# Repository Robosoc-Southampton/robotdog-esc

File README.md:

# Robot dog ESC

This is the repo for a FOC-based motor driver for a drone motor.

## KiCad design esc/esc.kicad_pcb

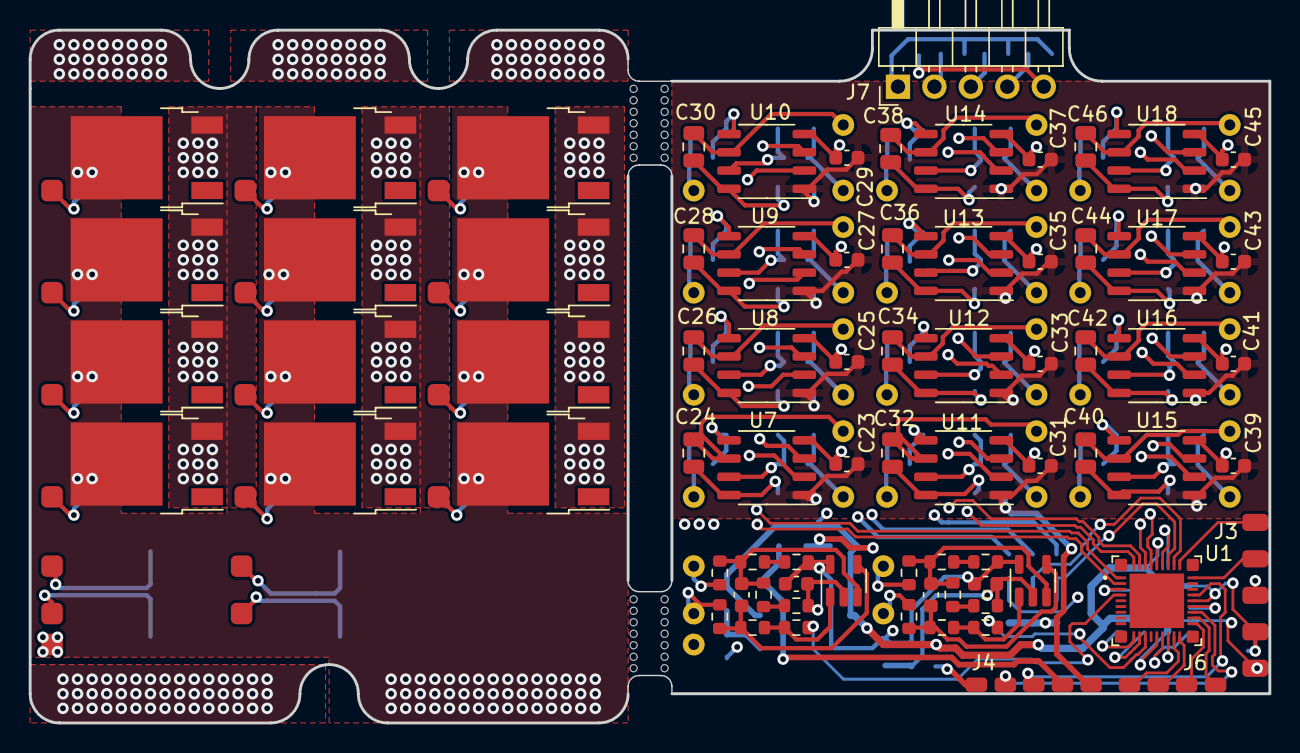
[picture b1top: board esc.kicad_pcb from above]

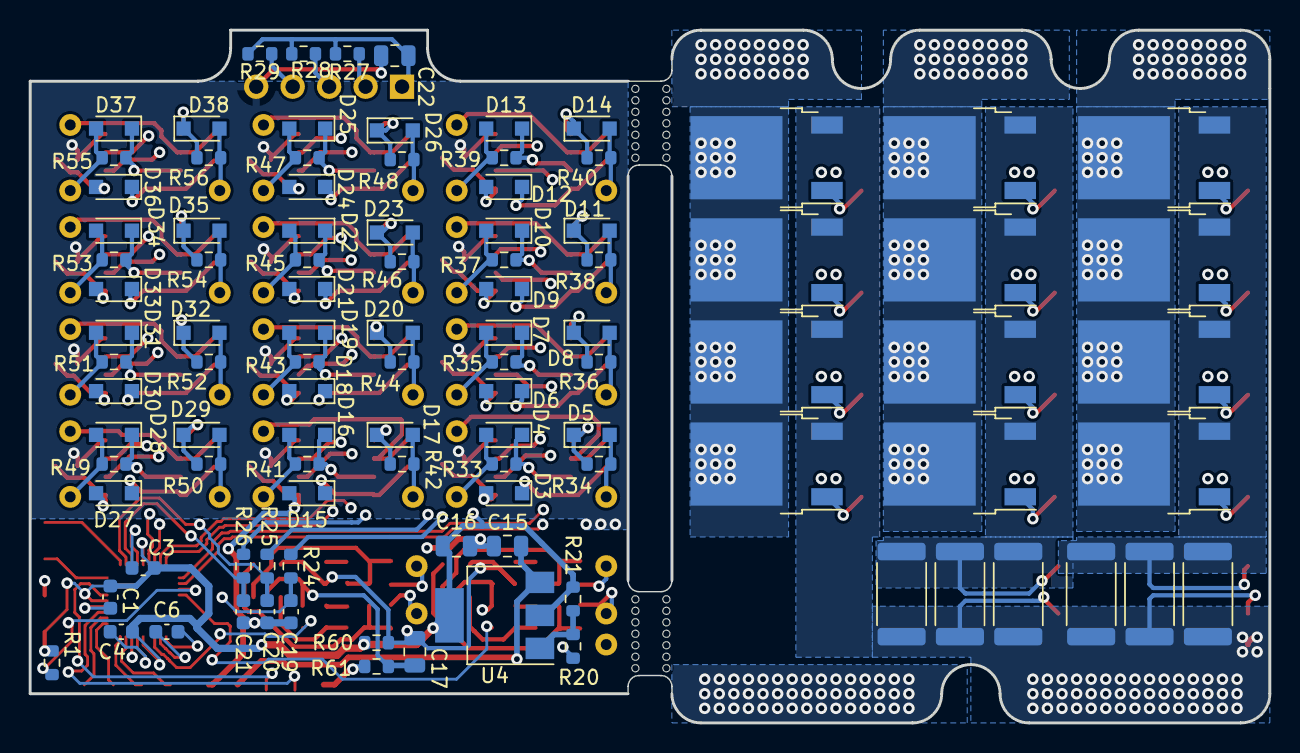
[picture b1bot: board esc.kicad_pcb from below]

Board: 4 copper layers, 86.4 x 48.3 mm, 234 parts (101 on the bottom side), 135 nets.

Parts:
C1, C3, C4, C6, C12, C13, C23, C25, C27, C29, C31, C33, C35, C37, C39, C41, C43, C45: 100n; C_0603_1608Metric
C8, C9, C19, C20, C21: 1n; C_0603_1608Metric
C15, C16, C17, C22, C24, C26, C28, C30, C32, C34, C36, C38, C40, C42, C44, C46: 10u; C_0805_2012Metric
D3, D4, D5, D6, D7, D8, D9, D10, D11, D12, D13, D14, D15, D16, D17, D18, D19, D20, D21, D22, D23, D24, D25, D26, D27, D28, D29, D30, D31, D32, D33, D34, D35, D36, D37, D38: 1N5819WS; D_SOD-323_HandSoldering
J3: Conn_01x05; ProgConnector
J4: Conn_01x05; EdgeConnector_5
J6: Conn_01x04; EdgeConnector_4
J7: Conn_01x05; PinHeader_1x05_P2.54mm_Horizontal
J8, J9, J10, J11, J17, J23, J29, J35, J41, J47, J53, J59, J65, J71, J77, J83, J88: Conn_01x01; SmallPad
J12, J13, J14, J18, J19, J20, J24, J25, J26, J30, J31, J32, J36, J37, J38, J42, J43, J44, J48, J49, J50, J54, J55, J56, J60, J61, J62, J66, J67, J68, J72, J73, J74, J78, J79, J80, J84, J85, J86, J87, J89: Conn_01x01; SmallPin
Q1, Q2, Q3, Q4, Q5, Q6, Q7, Q8, Q9, Q10, Q11, Q12, Q13, Q14, Q15, Q16, Q17, Q18, Q19, Q20, Q21, Q22, Q23, Q24: Q_NMOS_GDS; TO-252-2
R1: 10k; R_0603_1608Metric
R2, R3, R4, R5, R6, R7: 3m; R_2512_6332Metric
R8, R9, R10, R11: 120; R_0603_1608Metric
R16, R17, R18, R19, R22, R23, R30, R31, R32, R59: 3.3k; R_0603_1608Metric
R20: 1.5k; R_0603_1608Metric
R21, R24, R25, R26, R27, R28, R29: 1k; R_0603_1608Metric
R33, R34, R35, R36, R37, R38, R39, R40, R41, R42, R43, R44, R45, R46, R47, R48, R49, R50, R51, R52, R53, R54, R55, R56: 15; R_0603_1608Metric
R57, R58: 33; R_0603_1608Metric
R60, R61: 0R; R_0603_1608Metric
U1: dsPIC33CK64MC103; UQFN-36
U2, U3: GS8051; TSOT-23-5
U4: AP1117-ADJ; SOT-223-3_TabPin2
U7, U8, U9, U10, U11, U12, U13, U14, U15, U16, U17, U18: EG2131; SOP-8_3.9x4.9mm_P1.27mm

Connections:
+3.3VA: C6.1, C12.1, C13.1, C17.1, R30.2, R32.1, R60.2, U1.10 (AVDD), U2.5 (V+), U3.5 (V+)
+3V3: C1.2, C3.2, C4.2, C16.1, C22.1, J3.2, J7.1, R1.1, R21.1, R27.1, R28.1, R29.1, R60.1, U1.14 (VDD), U1.23 (VDD), U1.32 (VDD), U4.2 (VO)
+5V: C15.1, J4.4, U4.3 (VI)
+12V: C23.1, C25.1, C27.1, C29.1, C31.1, C33.1, C35.1, C37.1, C39.1, C41.1, C43.1, C45.1, D3.2 (A), D6.2 (A), D9.2 (A), D12.2 (A), D15.2 (A), D18.2 (A), D21.2 (A), D24.2 (A), D27.2 (A), D30.2 (A), D33.2 (A), D36.2 (A), J4.5, U7.1 (VCC), U8.1 (VCC), U9.1 (VCC), U10.1 (VCC), U11.1 (VCC), U12.1 (VCC), U13.1 (VCC), U14.1 (VCC), U15.1 (VCC), U16.1 (VCC), U17.1 (VCC), U18.1 (VCC)
/GPIO0: J6.1, U1.17 (OSCI/CLKI/AN5/RP32/RB0)
/GPIO1: J6.2, U1.18 (OSCO/CLKO/AN6/RP33/RB1)
/GPIO2: J6.3, U1.19 (OA2OUT/AN1/AN7/CMP1D/RP34/INT0/RB2)
/GPIO3: J6.4, U1.20 (PGD2/OA2IN-/AN8/RP35/RB3)
/HOME/HALL_C: C21.1, R26.1, U1.30 (RP53/RC5)
/I2C_SCL: J4.2, U1.21 (PGC2/OA2IN+/RP36/RB4)
/I2C_SDA: J4.3, U1.24 (PGD3/RP37/RB5)
/PGC1: J3.5, U1.28 (PGC1/AN11/RP41/SDA1/RB9)
/PGD1: J3.4, U1.27 (PGD1/AN10/RP40/SCL1/RB8)
/Phases/A_CURRENT_SENSE: R57.1, U1.4 (AN12/RP48/RC0)
/Phases/A_HIN: U1.1 (RP46/PWM1H/RB14), U7.2 (HIN), U8.2 (HIN), U9.2 (HIN), U10.2 (HIN)
/Phases/B_CURRENT_SENSE: R58.1, U1.12 (OA3IN-/AN13/CMP1B/ISRC0/RP49/RC1)
/Phases/B_HIN: U1.35 (TDI/RP44/PWM2H/RB12), U11.2 (HIN), U12.2 (HIN), U13.2 (HIN), U14.2 (HIN)
/Phases/C_HIN: U1.33 (TMS/RP42/PWM3H/RB10), U15.2 (HIN), U16.2 (HIN), U17.2 (HIN), U18.2 (HIN)
/Phases/PHASE_A: Q1.3 (S), Q2.2 (D), Q3.3 (S), Q4.2 (D), Q5.3 (S), Q6.2 (D), Q7.3 (S), Q8.2 (D)
/Phases/PHASE_B: Q9.3 (S), Q10.2 (D), Q11.3 (S), Q12.2 (D), Q13.3 (S), Q14.2 (D), Q15.3 (S), Q16.2 (D)
/Phases/PHASE_C: Q17.3 (S), Q18.2 (D), Q19.3 (S), Q20.2 (D), Q21.3 (S), Q22.2 (D), Q23.3 (S), Q24.2 (D)
/Phases/Phase A/BRIDGE_LOW: J8.1, Q2.3 (S), Q4.3 (S), Q6.3 (S), Q8.3 (S), R2.1, R3.1, R4.1
/Phases/Phase B/BRIDGE_LOW: J10.1, Q10.3 (S), Q12.3 (S), Q14.3 (S), Q16.3 (S), R5.1, R6.1, R7.1
/Phases/~A_LIN: U1.2 (RP47/PWM1L/RB15), U7.3 (~LIN), U8.3 (~LIN), U9.3 (~LIN), U10.3 (~LIN)
/Phases/~B_LIN: U1.36 (RP45/PWM2L/RB13), U11.3 (~LIN), U12.3 (~LIN), U13.3 (~LIN), U14.3 (~LIN)
/Phases/~C_LIN: U1.34 (TCK/RP43/PWM3L/RB11), U15.3 (~LIN), U16.3 (~LIN), U17.3 (~LIN), U18.3 (~LIN)
/QEI_A/HALL_A: C19.1, R24.1, U1.16 (AN15/IBIAS2/RP51/RC3)
/QEI_B/HALL_B: C20.1, R25.1, U1.29 (RP52/RC4)
/~MCLR: J3.1, R1.2, U1.3 (~MCLR)
GND: C1.1, C3.1, C4.1, C15.2, C16.2, C19.2, C20.2, C21.2, C22.2, C23.2, C25.2, C27.2, C29.2, C31.2, C33.2, C35.2, C37.2, C39.2, C41.2, C43.2, C45.2, J3.3, J4.1, J7.5, J89.1, R20.2, R61.1, U1.15 (VSS), U1.22 (VSS), U1.31 (VSS), U7.4 (COM), U8.4 (COM), U9.4 (COM), U10.4 (COM), U11.4 (COM), U12.4 (COM), U13.4 (COM), U14.4 (COM), U15.4 (COM), U16.4 (COM), U17.4 (COM), U18.4 (COM)
GNDA: C6.2, C12.2, C13.2, C17.2, R31.1, R59.2, R61.2, U1.11 (AVSS), U2.2 (V-), U3.2 (V-)
GNDPWR: J9.1, J11.1, J88.1, Q18.3 (S), Q20.3 (S), Q22.3 (S), Q24.3 (S), R2.2, R3.2, R4.2, R5.2, R6.2, R7.2
unnamed: C8.1, R8.1, R16.1, R17.2, U2.3 (+)
unnamed: C8.2, R9.1, R22.2, U2.4 (-)
unnamed: C9.1, R10.1, R18.1, R19.2, U3.3 (+)
unnamed: C9.2, R11.1, R23.2, U3.4 (-)
unnamed: C24.1, D3.1 (K), U7.8 (VB)
unnamed: C24.2, J13.1, U7.6 (VS)
unnamed: C26.1, D6.1 (K), U8.8 (VB)
unnamed: C26.2, J19.1, U8.6 (VS)
unnamed: C28.1, D9.1 (K), U9.8 (VB)
unnamed: C28.2, J25.1, U9.6 (VS)
unnamed: C30.1, D12.1 (K), U10.8 (VB)
unnamed: C30.2, J31.1, U10.6 (VS)
unnamed: C32.1, D15.1 (K), U11.8 (VB)
unnamed: C32.2, J37.1, U11.6 (VS)
unnamed: C34.1, D18.1 (K), U12.8 (VB)
unnamed: C34.2, J43.1, U12.6 (VS)
unnamed: C36.1, D21.1 (K), U13.8 (VB)
unnamed: C36.2, J49.1, U13.6 (VS)
unnamed: C38.1, D24.1 (K), U14.8 (VB)
unnamed: C38.2, J55.1, U14.6 (VS)
unnamed: C40.1, D27.1 (K), U15.8 (VB)
unnamed: C40.2, J61.1, U15.6 (VS)
unnamed: C42.1, D30.1 (K), U16.8 (VB)
unnamed: C42.2, J67.1, U16.6 (VS)
unnamed: C44.1, D33.1 (K), U17.8 (VB)
unnamed: C44.2, J73.1, U17.6 (VS)
unnamed: C46.1, D36.1 (K), U18.8 (VB)
unnamed: C46.2, J79.1, U18.6 (VS)
unnamed: D4.1 (K), R33.1, U7.7 (HO)
unnamed: D4.2 (A), J12.1, R33.2
unnamed: D5.1 (K), R34.1, U7.5 (LO)
unnamed: D5.2 (A), J14.1, R34.2
unnamed: D7.1 (K), R35.1, U8.7 (HO)
unnamed: D7.2 (A), J18.1, R35.2
unnamed: D8.1 (K), R36.1, U8.5 (LO)
unnamed: D8.2 (A), J20.1, R36.2
unnamed: D10.1 (K), R37.1, U9.7 (HO)
unnamed: D10.2 (A), J24.1, R37.2
unnamed: D11.1 (K), R38.1, U9.5 (LO)
unnamed: D11.2 (A), J26.1, R38.2
unnamed: D13.1 (K), R39.1, U10.7 (HO)
unnamed: D13.2 (A), J30.1, R39.2
unnamed: D14.1 (K), R40.1, U10.5 (LO)
unnamed: D14.2 (A), J32.1, R40.2
unnamed: D16.1 (K), R41.1, U11.7 (HO)
unnamed: D16.2 (A), J36.1, R41.2
unnamed: D17.1 (K), R42.1, U11.5 (LO)
unnamed: D17.2 (A), J38.1, R42.2
unnamed: D19.1 (K), R43.1, U12.7 (HO)
unnamed: D19.2 (A), J42.1, R43.2
unnamed: D20.1 (K), R44.1, U12.5 (LO)
unnamed: D20.2 (A), J44.1, R44.2
unnamed: D22.1 (K), R45.1, U13.7 (HO)
unnamed: D22.2 (A), J48.1, R45.2
unnamed: D23.1 (K), R46.1, U13.5 (LO)
unnamed: D23.2 (A), J50.1, R46.2
unnamed: D25.1 (K), R47.1, U14.7 (HO)
unnamed: D25.2 (A), J54.1, R47.2
unnamed: D26.1 (K), R48.1, U14.5 (LO)
unnamed: D26.2 (A), J56.1, R48.2
unnamed: D28.1 (K), R49.1, U15.7 (HO)
unnamed: D28.2 (A), J60.1, R49.2
unnamed: D29.1 (K), R50.1, U15.5 (LO)
unnamed: D29.2 (A), J62.1, R50.2
unnamed: D31.1 (K), R51.1, U16.7 (HO)
unnamed: D31.2 (A), J66.1, R51.2
unnamed: D32.1 (K), R52.1, U16.5 (LO)
unnamed: D32.2 (A), J68.1, R52.2
unnamed: D34.1 (K), R53.1, U17.7 (HO)
unnamed: D34.2 (A), J72.1, R53.2
unnamed: D35.1 (K), R54.1, U17.5 (LO)
unnamed: D35.2 (A), J74.1, R54.2
unnamed: D37.1 (K), R55.1, U18.7 (HO)
unnamed: D37.2 (A), J78.1, R55.2
unnamed: D38.1 (K), R56.1, U18.5 (LO)
unnamed: D38.2 (A), J80.1, R56.2
unnamed: J7.2, R24.2, R27.2
unnamed: J7.3, R25.2, R28.2
unnamed: J7.4, R26.2, R29.2
unnamed: J17.1, Q2.1 (G)
unnamed: J23.1, Q4.1 (G)
unnamed: J29.1, Q6.1 (G)
unnamed: J35.1, Q8.1 (G)
unnamed: J41.1, Q10.1 (G)
unnamed: J47.1, Q12.1 (G)
unnamed: J53.1, Q14.1 (G)
unnamed: J59.1, Q16.1 (G)
unnamed: J65.1, Q18.1 (G)
unnamed: J71.1, Q20.1 (G)
unnamed: J77.1, Q22.1 (G)
unnamed: J83.1, Q24.1 (G)
unnamed: J84.1, R8.2
unnamed: J85.1, R9.2
unnamed: J86.1, R10.2
unnamed: J87.1, R11.2
unnamed: R16.2, R30.1
unnamed: R17.1, R31.2
unnamed: R18.2, R32.2
unnamed: R19.1, R59.1
unnamed: R20.1, R21.2, U4.1 (ADJ)
unnamed: R22.1, R57.2, U2.1
unnamed: R23.1, R58.2, U3.1
VDD: Q1.2 (D), Q3.2 (D), Q5.2 (D), Q7.2 (D), Q9.2 (D), Q11.2 (D), Q13.2 (D), Q15.2 (D), Q17.2 (D), Q19.2 (D), Q21.2 (D), Q23.2 (D)

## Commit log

2021-10-24 Initial commit.
    design-notes.md is a document I created to summarize all the
    considerations to be taken into account when designing a FOC motor
    driver.
    Makefile can be used to export this to HTML. It uses pandoc.
2021-10-24 Added README.md
2022-03-02 Started schematic
2022-03-25 Finished layout
2022-04-18 Finished design - first submission
2022-09-19 Working version
2022-09-25 Code files
2022-11-03 Some stuff
2022-11-11 Pretty much finished new design
2022-11-30 (Tentatively) final design
2023-02-04 Sample reading works!
